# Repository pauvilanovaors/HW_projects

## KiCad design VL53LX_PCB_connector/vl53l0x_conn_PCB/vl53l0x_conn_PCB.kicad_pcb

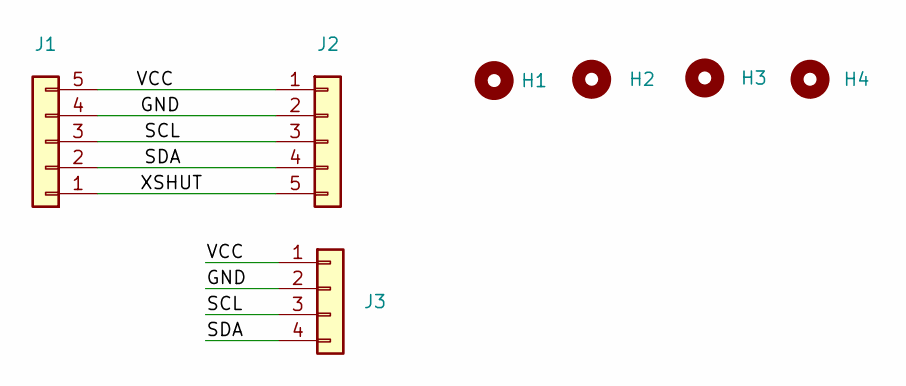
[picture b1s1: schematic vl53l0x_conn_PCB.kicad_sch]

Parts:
H1, H2, H3, H4: MountingHole; MountingHole_2.2mm_M2_DIN965_Pad
J1, J2: Conn_01x05; Conn_5pins
J3: Conn_01x04; Conn_4pins

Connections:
/GND: J1.4, J2.2, J3.2
/SCL: J1.3, J2.3, J3.3
/SDA: J1.2, J2.4, J3.4
/VCC: J1.5, J2.1, J3.1
/XSHUT: J1.1, J2.5

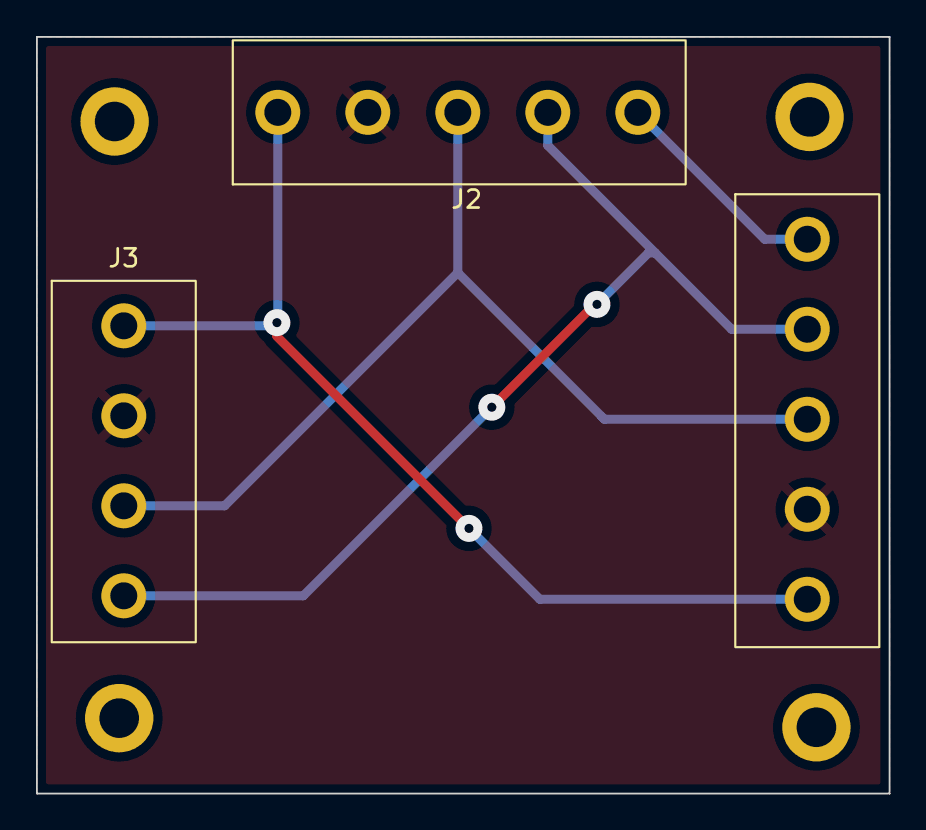
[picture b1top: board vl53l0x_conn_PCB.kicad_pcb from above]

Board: 2 copper layers, 47.4 x 42.0 mm, 7 parts (0 on the bottom side), 5 nets.

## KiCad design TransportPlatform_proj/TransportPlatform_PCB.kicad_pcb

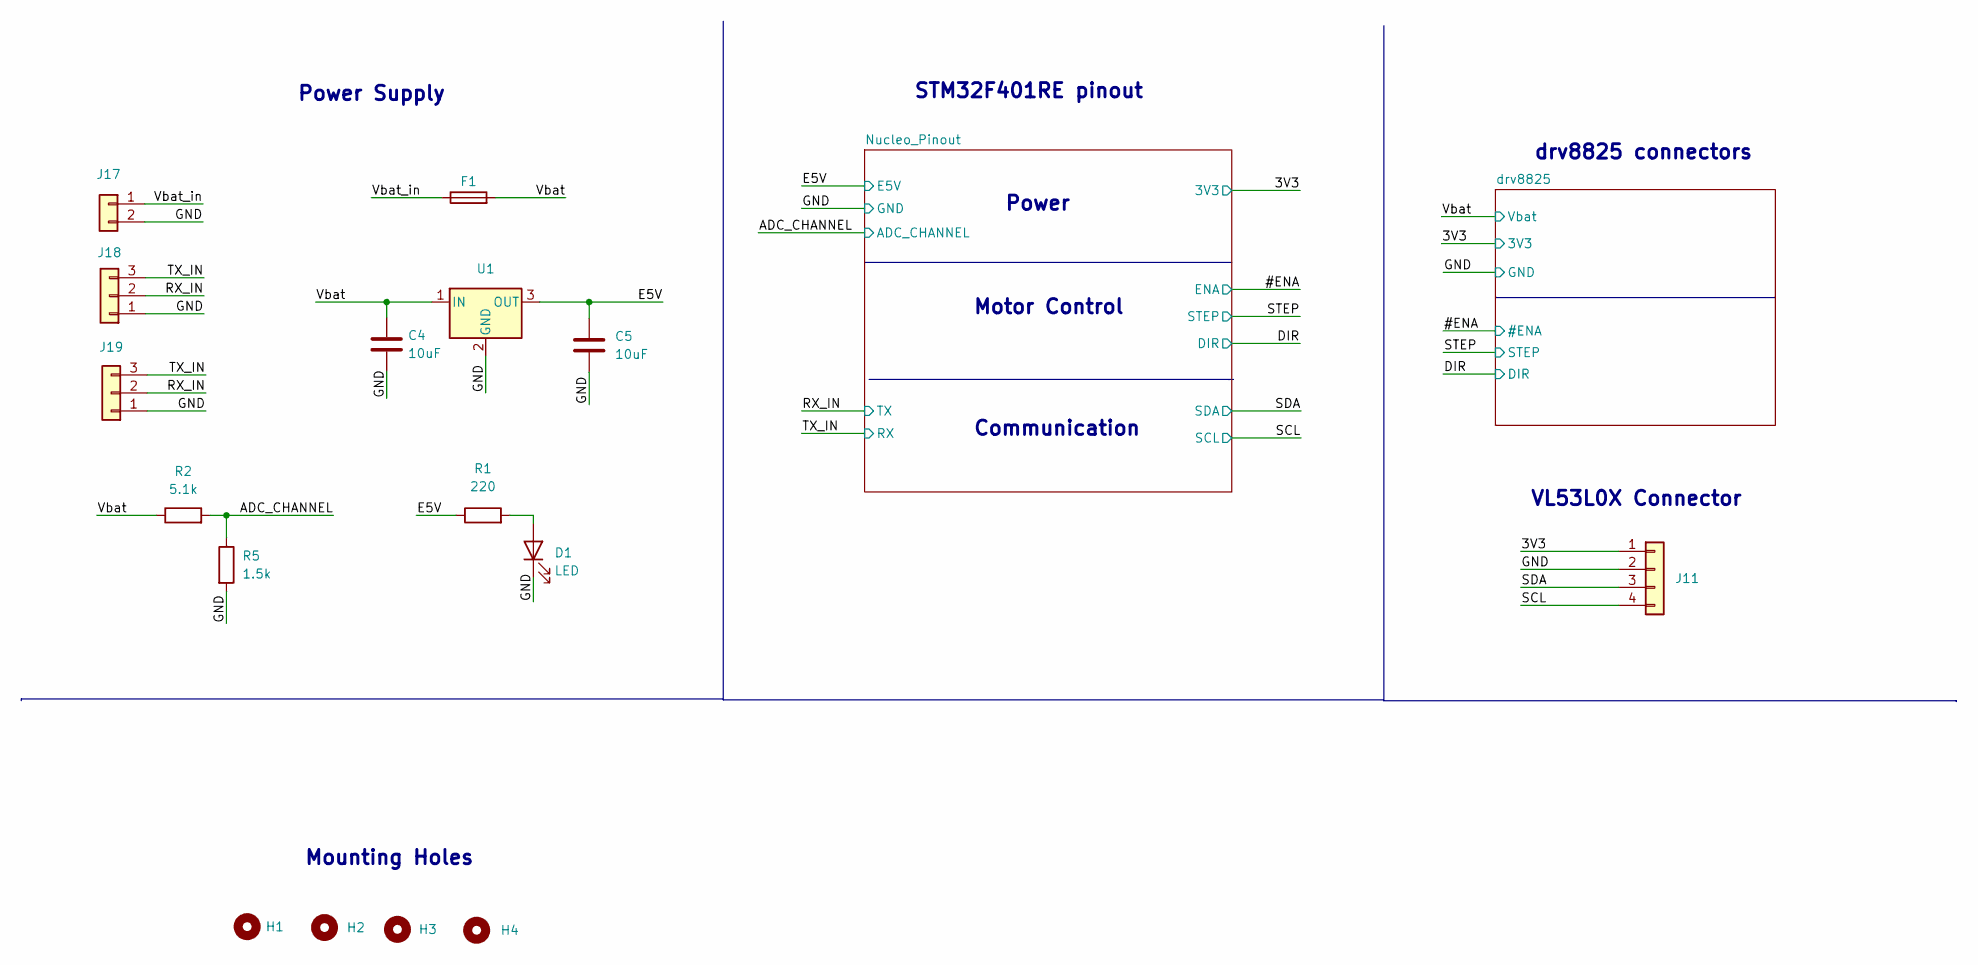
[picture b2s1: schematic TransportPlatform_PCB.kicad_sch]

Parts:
C4, C5: 10uF; CP_Radial_D5.0mm_P2.50mm
D1: LED; pwr_LED
F1: Fuse; portafusible
H1, H2, H3, H4: MountingHole; MountingHole_2.5mm_Pad
J11: Conn_01x04; PinHeader_1x04_P2.54mm_Vertical
J17: Conn_01x02; BAT_connector
J18: Conn_01x03; PinHeader_1x03_P2.54mm_Vertical
J19: Conn_01x03; Uart_conn
R1: 220; R_Axial_DIN0207_L6.3mm_D2.5mm_P10.16mm_Horizontal
R2: 5.1k; R_Axial_DIN0207_L6.3mm_D2.5mm_P10.16mm_Horizontal
R5: 1.5k; R_Axial_DIN0207_L6.3mm_D2.5mm_P10.16mm_Horizontal
U1: R-78E5.0-0.5; Converter_DCDC_RECOM_R-78E-0.5_THT

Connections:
/3V3: J11.1; also elsewhere on the board
/ADC_CHANNEL: R2.2, R5.1; also elsewhere on the board
/E5V: C5.1, R1.1, U1.3 (OUT); also elsewhere on the board
/GND: C4.2, C5.2, D1.1 (K), J11.2, J17.2, J18.1, J19.1, R5.2, U1.2 (GND); also elsewhere on the board
/RX_IN: J18.2, J19.2; also elsewhere on the board
/SCL: J11.4; also elsewhere on the board
/SDA: J11.3; also elsewhere on the board
/TX_IN: J18.3, J19.3; also elsewhere on the board
/Vbat: C4.1, F1.2, R2.1, U1.1 (IN); also elsewhere on the board
/Vbat_in: F1.1, J17.1
unnamed: D1.2 (A), R1.2

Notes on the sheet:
STM32F401RE pinout
drv8825 connectors
Power Supply
Mounting Holes
Communication
VL53L0X Connector
Power
Motor Control

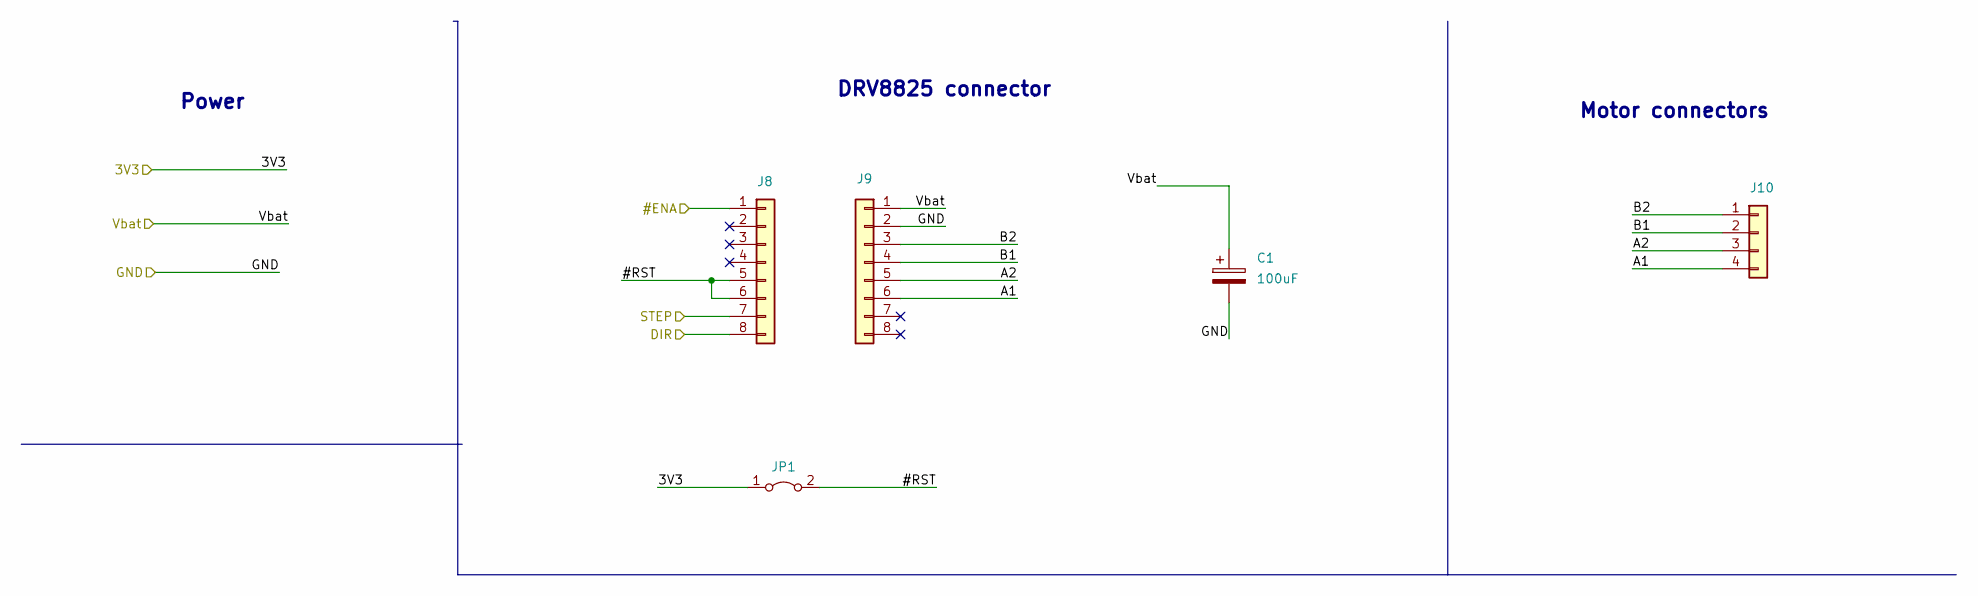
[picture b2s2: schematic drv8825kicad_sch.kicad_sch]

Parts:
C1: 100uF; CP_Radial_D5.0mm_P2.50mm
J8, J9: Conn_01x08; PinSocket_1x08_P2.54mm_Vertical
J10: Conn_01x04; PinSocket_1x04_P2.54mm_Vertical
JP1: Jumper_2_Bridged; PinHeader_1x02_P2.54mm_Vertical

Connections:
/3V3: JP1.1 (A); also elsewhere on the board
/#ENA: J8.1; also elsewhere on the board
/DIR: J8.8; also elsewhere on the board
/GND: C1.2, J9.2; also elsewhere on the board
/STEP: J8.7; also elsewhere on the board
/Vbat: C1.1, J9.1; also elsewhere on the board
/drv8825/#RST: J8.5, J8.6, JP1.2 (B)
/drv8825/A1: J9.6, J10.4
/drv8825/A2: J9.5, J10.3
/drv8825/B1: J9.4, J10.2
/drv8825/B2: J9.3, J10.1

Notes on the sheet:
DRV8825 connector
Motor connectors
Power

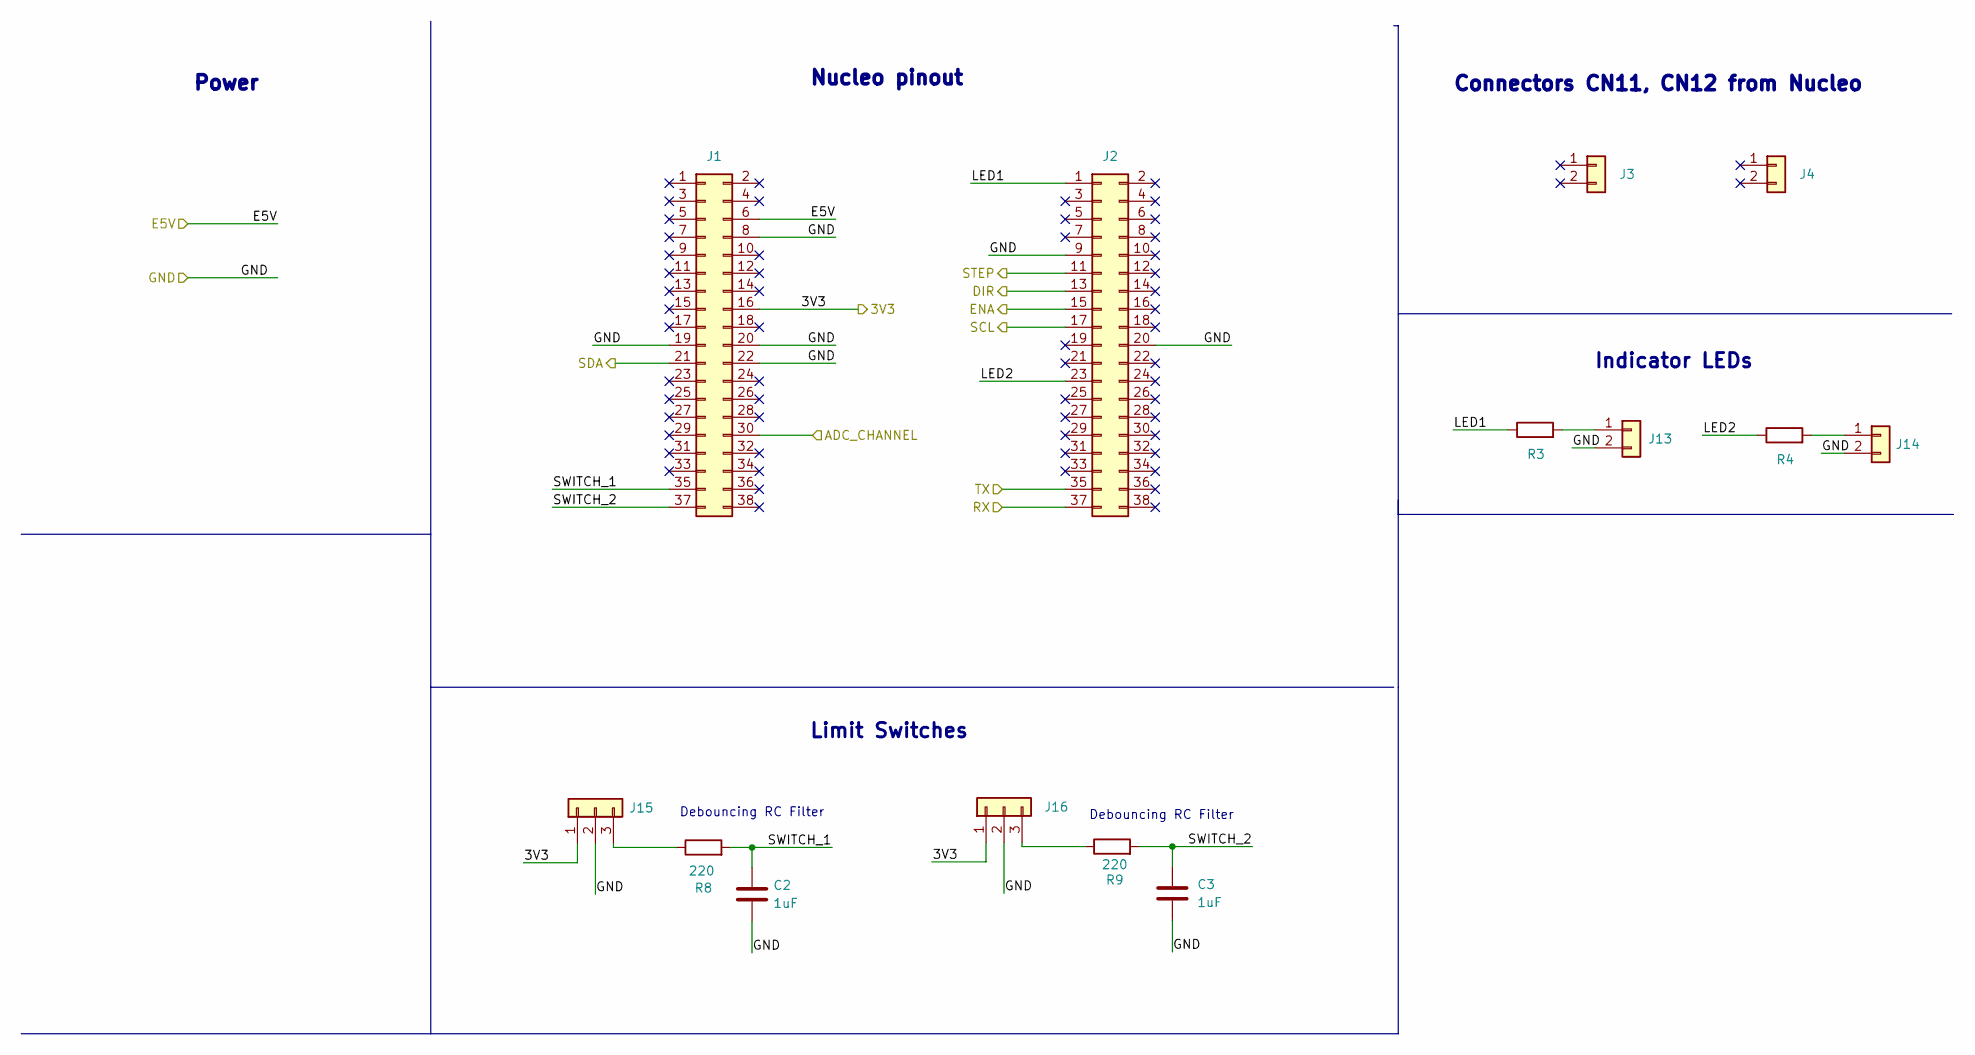
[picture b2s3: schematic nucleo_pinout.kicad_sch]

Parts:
C2, C3: 1uF; CP_Radial_D5.0mm_P2.50mm
J1, J2: Conn_02x19_Odd_Even; PinSocket_2x19_P2.54mm_Vertical
J3, J4: Conn_01x02; PinSocket_1x02_P2.54mm_Vertical
J13, J14: Conn_01x02; PinHeader_1x02_P2.54mm_Vertical
J15, J16: Conn_01x03; PinHeader_1x03_P2.54mm_Vertical
R3, R4, R8, R9: 220; R_Axial_DIN0207_L6.3mm_D2.5mm_P10.16mm_Horizontal

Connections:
/3V3: J1.16, J15.1, J16.1; also elsewhere on the board
/#ENA: J2.15; also elsewhere on the board
/ADC_CHANNEL: J1.30; also elsewhere on the board
/DIR: J2.13; also elsewhere on the board
/E5V: J1.6; also elsewhere on the board
/GND: C2.2, C3.2, J1.8, J1.19, J1.20, J1.22, J2.9, J2.20, J13.2, J14.2, J15.2, J16.2; also elsewhere on the board
/Nucleo_Pinout/LED1: J2.1, R3.1
/Nucleo_Pinout/LED2: J2.23, R4.1
/Nucleo_Pinout/SWITCH_1: C2.1, J1.35, R8.2
/Nucleo_Pinout/SWITCH_2: C3.1, J1.37, R9.2
/RX_IN: J2.35; also elsewhere on the board
/SCL: J2.17; also elsewhere on the board
/SDA: J1.21; also elsewhere on the board
/STEP: J2.11; also elsewhere on the board
/TX_IN: J2.37; also elsewhere on the board
unnamed: J13.1, R3.2
unnamed: J14.1, R4.2
unnamed: J15.3, R8.1
unnamed: J16.3, R9.1

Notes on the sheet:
Connectors CN11, CN12 from Nucleo
Indicator LEDs
Debouncing RC Filter
Nucleo pinout
Power
Limit Switches

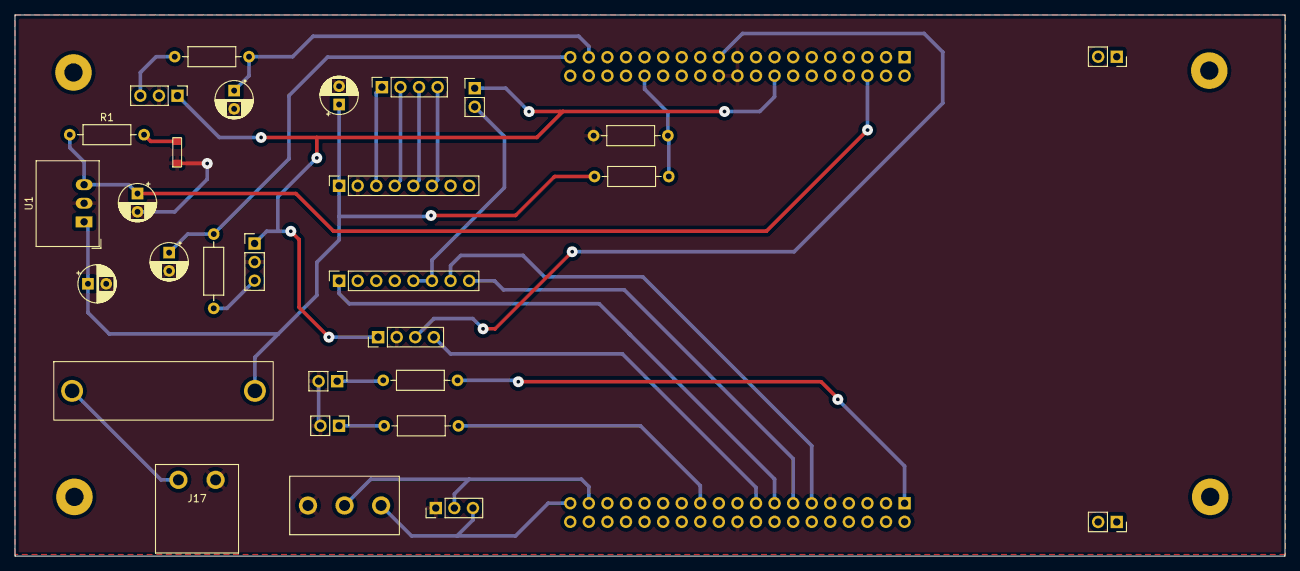
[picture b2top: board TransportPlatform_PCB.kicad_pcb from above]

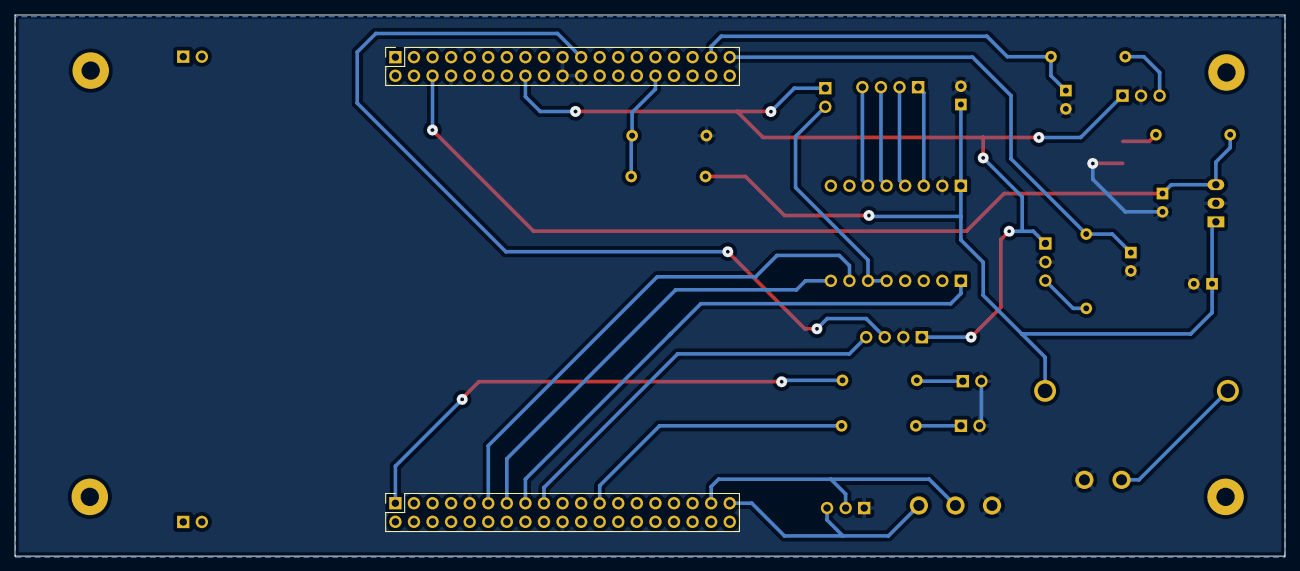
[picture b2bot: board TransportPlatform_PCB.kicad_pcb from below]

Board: 2 copper layers, 173.7 x 74.0 mm, 35 parts (2 on the bottom side), 27 nets.

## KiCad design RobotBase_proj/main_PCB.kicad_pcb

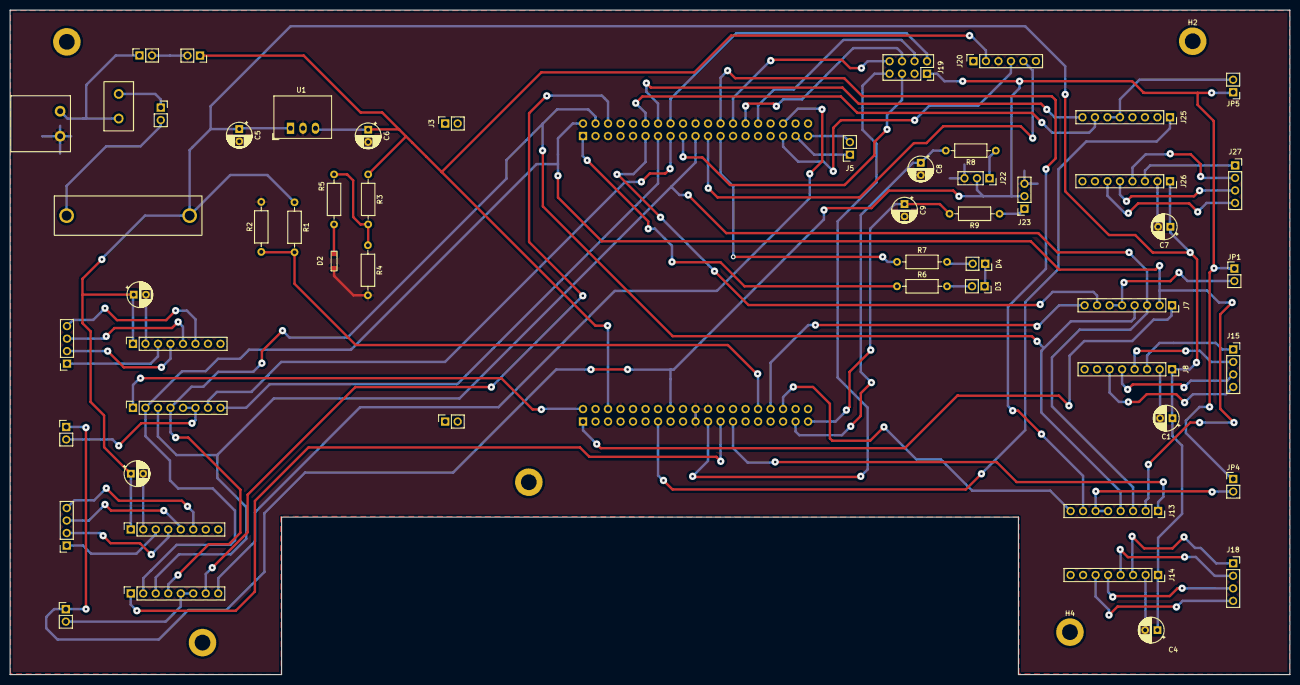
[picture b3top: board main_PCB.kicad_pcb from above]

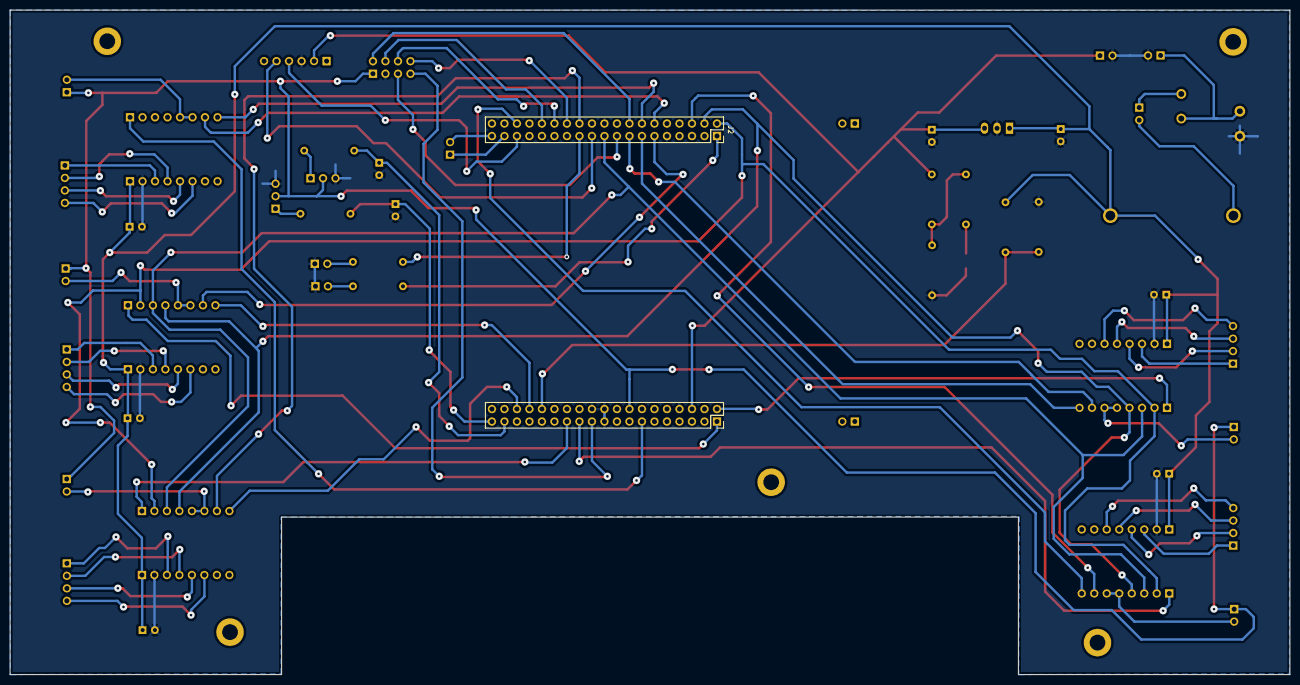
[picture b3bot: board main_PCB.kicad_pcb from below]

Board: 2 copper layers, 260.0 x 135.0 mm, 62 parts (2 on the bottom side), 71 nets.

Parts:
C1, C2, C3, C4, C7: 100uF; CP_Radial_D5.0mm_P2.50mm
C5, C6: 10uF; CP_Radial_D5.0mm_P2.50mm
C8, C9: 1uF; CP_Radial_D5.0mm_P2.50mm
D2: LED; pwr_LED
D3: USER_LED; PinSocket_1x02_P2.54mm_Vertical
D4: VBAT_LED; PinSocket_1x02_P2.54mm_Vertical
F1: Fusible; portafusible
H1, H2, H3, H4, H5: MountingHole; MountingHole_3.2mm_M3_DIN965_Pad
J1, J2: Conn_02x19_Odd_Even; PinSocket_2x19_P2.54mm_Vertical
J3, J4, J5, J28, J29: Conn_01x02; PinSocket_1x02_P2.54mm_Vertical
J7, J8, J9, J10, J11, J12, J13, J14, J25, J26: Conn_01x08; PinSocket_1x08_P2.54mm_Vertical
J15, J16, J17, J18, J27: Conn_01x04; PinSocket_1x04_P2.54mm_Vertical
J19: Conn_02x04_Top_Bottom; PinSocket_2x04_P2.54mm_Vertical
J20: Conn_01x06; PinSocket_1x06_P2.54mm_Vertical
J21: Vbat_connector; BAT_connector
J22: Limit_Switch_1; PinSocket_1x03_P2.54mm_Vertical
J23: Limit_Switch_2; PinSocket_1x03_P2.54mm_Vertical
J24: Power_Switch; PinSocket_1x02_P2.54mm_Vertical
JP1, JP2, JP3, JP4, JP5: Jumper_2_Bridged; PinHeader_1x02_P2.54mm_Vertical
R1: 5.1k; R_Axial_DIN0207_L6.3mm_D2.5mm_P10.16mm_Horizontal
R2, R4: 1.5k; R_Axial_DIN0207_L6.3mm_D2.5mm_P10.16mm_Horizontal
R3: 2.2k; R_Axial_DIN0207_L6.3mm_D2.5mm_P10.16mm_Horizontal
R5, R6, R7, R8, R9: 220; R_Axial_DIN0207_L6.3mm_D2.5mm_P10.16mm_Horizontal
SW1: Emergency_Button; emergency_button
U1: R-78E5.0-0.5; Converter_DCDC_RECOM_R-78E-0.5_THT

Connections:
/3V3: J1.16, J19.1, J22.2, J23.2, JP1.1 (A), JP2.1 (A), JP3.1 (A), JP4.1 (A), JP5.1 (A)
/#ENA_1: J1.1, J7.1
/#ENA_2: J1.2, J9.1
/#ENA_3: J1.23, J11.1
/#ENA_4: J1.25, J13.1
/#ENA_5: J1.13, J25.1
/ADC_CHANNEL: J1.30, R1.2, R2.1
/DIR_1: J1.32, J7.8
/DIR_2: J2.13, J9.8
/DIR_3: J2.34, J11.8
/DIR_4: J1.34, J13.8
/DIR_5: J2.14, J25.8
/E5V: C6.1, J1.6, J20.2, J29.1, R3.1, U1.3 (OUT)
/I2C_SCL: J2.17, J19.5
/I2C_SDA: J1.21, J19.7
/M0: J2.2, J7.2, J9.2, J11.2, J13.2
/M1: J2.19, J7.3, J9.3, J11.3, J13.3
/M2: J2.4, J7.4, J9.4, J11.4, J13.4
/NUCLEO_pinout/LIMIT_SWITCH_1: C8.1, J1.35, R8.2
/NUCLEO_pinout/LIMIT_SWITCH_2: C9.1, J1.37, R9.2
/NUCLEO_pinout/USART_RX_2: J2.37, J5.2
/NUCLEO_pinout/USART_TX_2: J2.35, J5.1
/NUCLEO_pinout/USER_LED: J2.1, R6.1
/NUCLEO_pinout/VBAT_LED: J2.23, R7.1
/PWR_SUPPLY/Vbat_in: J21.1, J28.1, SW1.1
/RX: J2.33, J20.4
/STEP_1: J2.11, J7.7
/STEP_2: J2.15, J9.7
/STEP_3: J2.6, J11.7
/STEP_4: J2.24, J13.7
/STEP_5: J2.12, J25.7
/TX: J2.21, J20.5
/Vbat: C1.1, C2.1, C3.1, C4.1, C5.1, C7.1, F1.2, J8.1, J10.1, J12.1, J14.1, J26.1, R1.1, U1.1 (IN)
/XSHUT_1: J2.16, J19.2
/XSHUT_2: J2.30, J19.4
/XSHUT_3: J2.28, J19.6
/XSHUT_4: J2.26, J19.8
/drv8225_mecanumwheels/#RST_1: J7.5, J7.6, JP1.2 (B)
/drv8225_mecanumwheels/#RST_2: J9.5, J9.6, JP2.2 (B)
/drv8225_mecanumwheels/#RST_3: J11.5, J11.6, JP3.2 (B)
/drv8225_mecanumwheels/#RST_4: J13.5, J13.6, JP4.2 (B)
/drv8225_mecanumwheels/A1_MOTOR_1: J8.5, J15.3
/drv8225_mecanumwheels/A1_MOTOR_2: J10.5, J16.3
/drv8225_mecanumwheels/A1_MOTOR_3: J12.5, J17.3
/drv8225_mecanumwheels/A1_MOTOR_4: J14.5, J18.3
/drv8225_mecanumwheels/A2_MOTOR_1: J8.6, J15.4
/drv8225_mecanumwheels/A2_MOTOR_2: J10.6, J16.4
/drv8225_mecanumwheels/A2_MOTOR_3: J12.6, J17.4
/drv8225_mecanumwheels/A2_MOTOR_4: J14.6, J18.4
/drv8225_mecanumwheels/B1_MOTOR_1: J8.4, J15.2
/drv8225_mecanumwheels/B1_MOTOR_2: J10.4, J16.2
/drv8225_mecanumwheels/B1_MOTOR_3: J12.4, J17.2
/drv8225_mecanumwheels/B1_MOTOR_4: J14.4, J18.2
/drv8225_mecanumwheels/B2_MOTOR_1: J8.3, J15.1
/drv8225_mecanumwheels/B2_MOTOR_2: J10.3, J16.1
/drv8225_mecanumwheels/B2_MOTOR_3: J12.3, J17.1
/drv8225_mecanumwheels/B2_MOTOR_4: J14.3, J18.1
/drv8825_lifterstage/#RST_5: J25.5, J25.6, JP5.2 (B)
/drv8825_lifterstage/A1_MOTOR_5: J26.5, J27.3
/drv8825_lifterstage/A2_MOTOR_5: J26.6, J27.4
/drv8825_lifterstage/B1_MOTOR_5: J26.4, J27.2
/drv8825_lifterstage/B2_MOTOR_5: J26.3, J27.1
GND: C1.2, C2.2, C3.2, C4.2, C5.2, C6.2, C7.2, C8.2, C9.2, D2.1 (K), D3.1 (K), D4.1 (K), J1.8, J1.19, J1.20, J1.22, J2.9, J2.20, J8.2, J10.2, J12.2, J14.2, J19.3, J20.3, J21.2, J22.3, J23.3, J26.2, J28.2, J29.2, R2.2, R4.2, U1.2 (GND)
unnamed: D2.2 (A), R5.2
unnamed: D3.2 (A), R6.2
unnamed: D4.2 (A), R7.2
unnamed: F1.1, J24.2
unnamed: J22.1, R8.1
unnamed: J23.1, R9.1
unnamed: J24.1, SW1.2
unnamed: R3.2, R4.1, R5.1

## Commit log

2023-05-19 Projects added
